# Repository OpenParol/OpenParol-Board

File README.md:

# OpenParol Control board

OpenParol-board is an open-source controller for a 6-DOF robotic arm. It features six TMC5160T Pro drivers and a section containing two galvanically isolated CAN-FD buses, which can be used for communication with external (or future) modules and controllers. It also includes an isolated I/O section for connecting limit switches (both mechanical and NPN inductive types), as well as two galvanically isolated outputs and inputs (one of which supports an MCU interrupt).

> [!IMPORTANT]
> This is merely a hobby project; under no circumstances is it a professional project intended for industrial use!

> [!IMPORTANT]
> The current design is a development version and has not yet been tested. It is therefore best to wait for the official release.

<div align="center">
  <span style="display: inline-block; font-size: 1.25em; font-weight: 600; letter-spacing: 0.7px; margin-bottom: 20px;">Sponsors</span>
  
  <span style="display: inline-block; margin-top: 10px;">Thank you for helping to develop this project!</span>
</div>

---
<br>

<span style="font-size: 1.25em; font-weight: 600; letter-spacing: 0.7px;">🌟 Design compatible with and tested on the PAROL6 arm by [@PCrnjak](https://github.com/PCrnjak). Thank you for such a wonderful project!</span>

## Overview

The board is built around an **STM32G474VET6** microcontroller and is designed
to provide:

- six **TMC5160T** stepper-motor driver channels;
- isolated CAN interfaces using **ISO1042DWV** transceivers;
- galvanic isolation and isolated power rails for selected interfaces;
- USB-C 2.0 connectivity;
- an ARM JTAG/SWD debug connector;
- status indicators, test points, configuration jumpers, and pluggable
  motor/power connectors.

The exact electrical behavior, pin assignments, component values, and
connection details are defined by the KiCad source files and should be taken
from the schematic rather than inferred from this overview.

<span style="font-size: 1.25em; font-weight: 600; letter-spacing: 0.7px;">If you are interested in the software, check out the other repositories [here](https://github.com/orgs/OpenParol/repositories)</span>

## Requirements

- [Latest KiCad](https://www.kicad.org/) version or a compatible version that can open
  the project files;
- the repository cloned with its directory structure preserved, so that the
  project can resolve its custom libraries and 3D models.

## Development workflow

When modifying the design:

1. Make schematic changes first.
2. Annotate and update the PCB from the schematic.
3. Verify footprints, pin assignments, clearances, and isolation boundaries.
4. Review the 3D model placement and board constraints.
5. Run ERC and DRC.
6. Export manufacturing files only from a tagged or otherwise clearly
   identified revision.

Custom symbols and footprints are stored in `board/libraries/`. Their library
paths are configured by `board/sym-lib-table` and `board/fp-lib-table`; avoid
moving these files without updating the corresponding KiCad configuration.

## Contributing

Contributions are more than welcome. Before submitting a change:

- keep schematic and PCB changes synchronized;
- include or update custom library data when a new footprint or symbol is
  required;
- preserve the existing project-relative library paths;
- run ERC and DRC and describe any intentional exceptions;
- explain the changes that have been made.

## License

Unless stated otherwise for a particular third-party asset, this project is
provided under the **GNU General Public License v3.0**. See [LICENSE](LICENSE)
for the complete license text.

Third-party component datasheets, manufacturer models, and other external
assets may be subject to their own terms. Verify their licensing and
redistribution conditions before using them outside this repository.

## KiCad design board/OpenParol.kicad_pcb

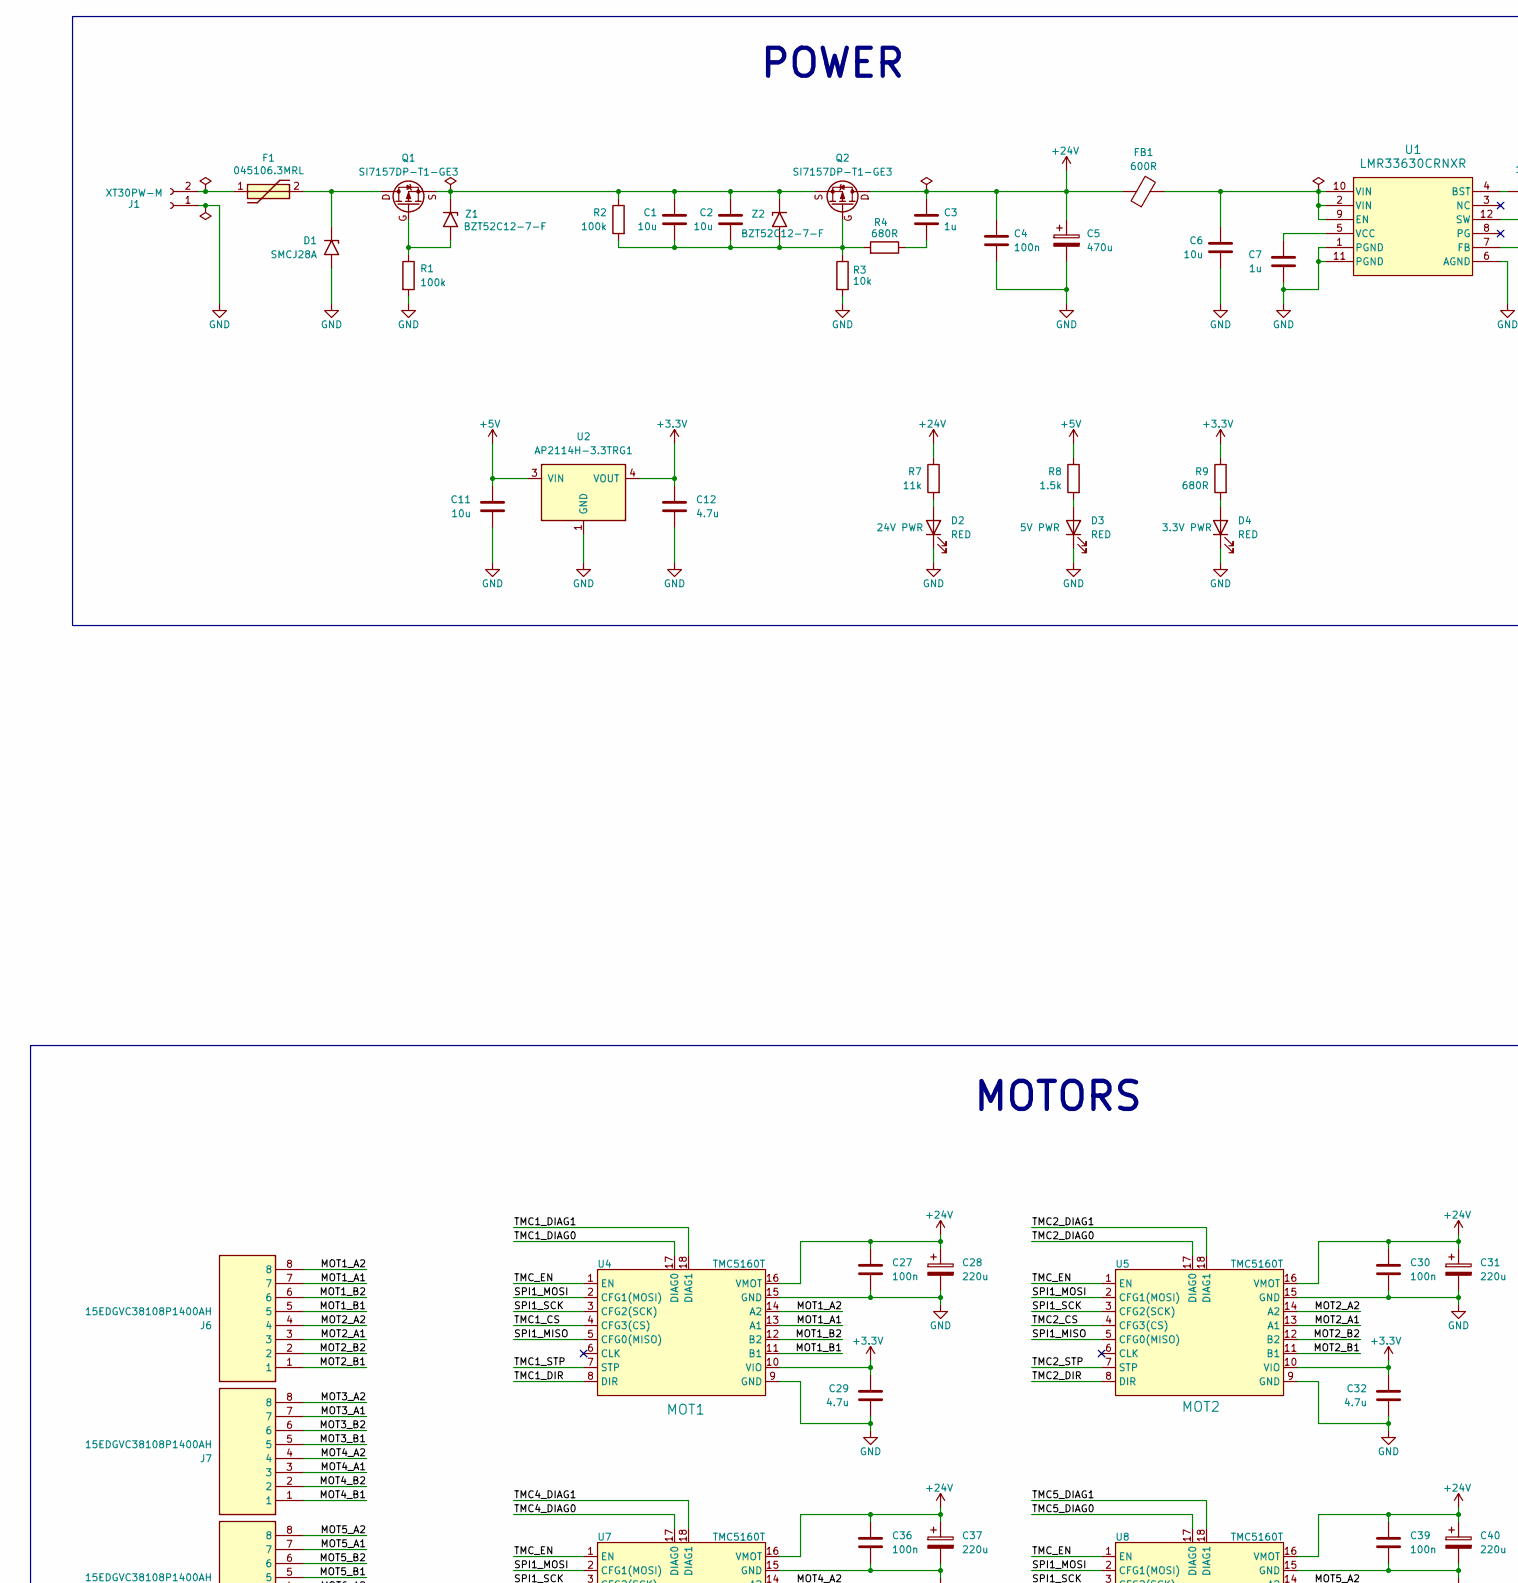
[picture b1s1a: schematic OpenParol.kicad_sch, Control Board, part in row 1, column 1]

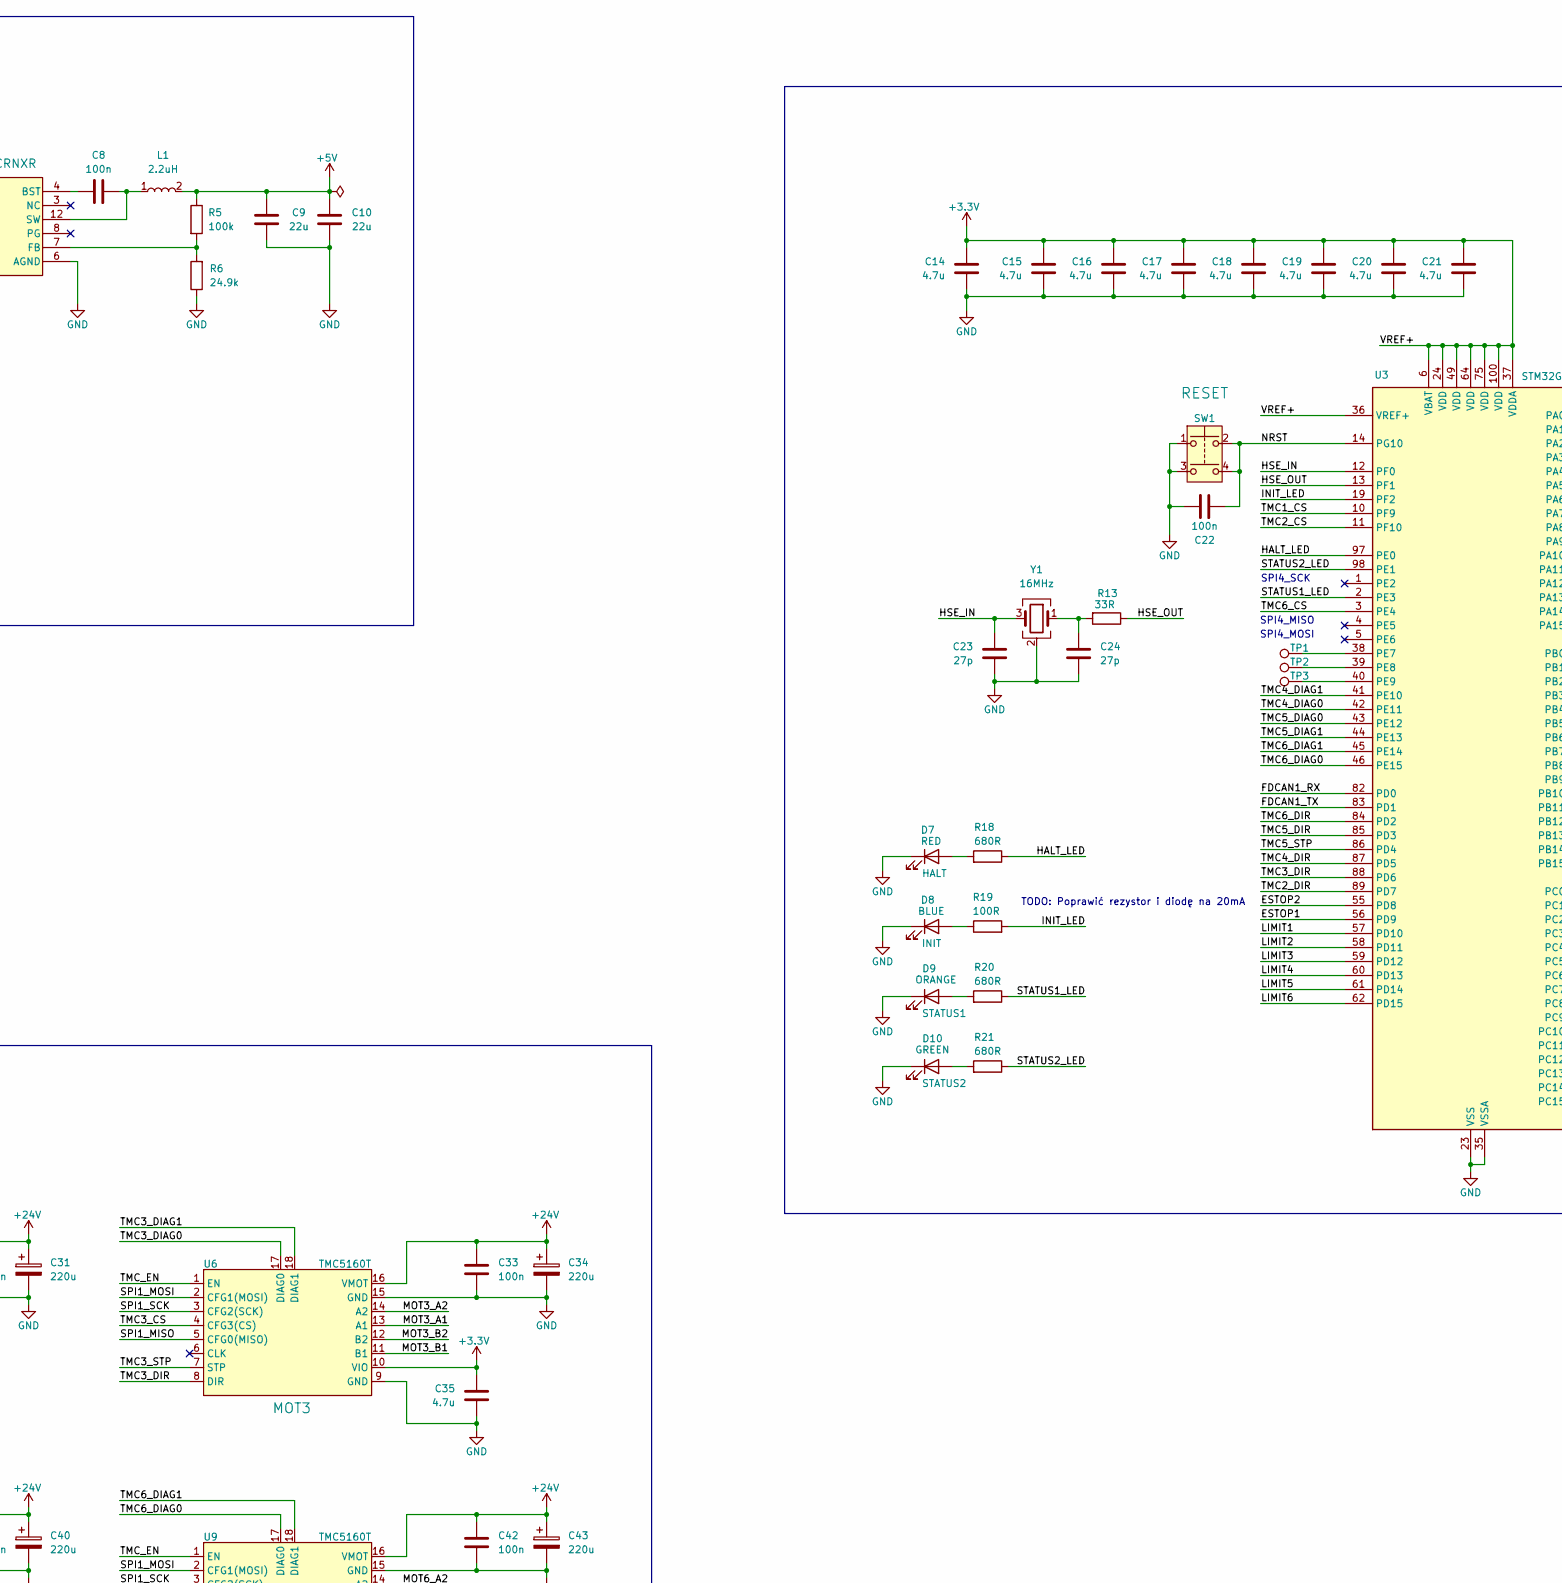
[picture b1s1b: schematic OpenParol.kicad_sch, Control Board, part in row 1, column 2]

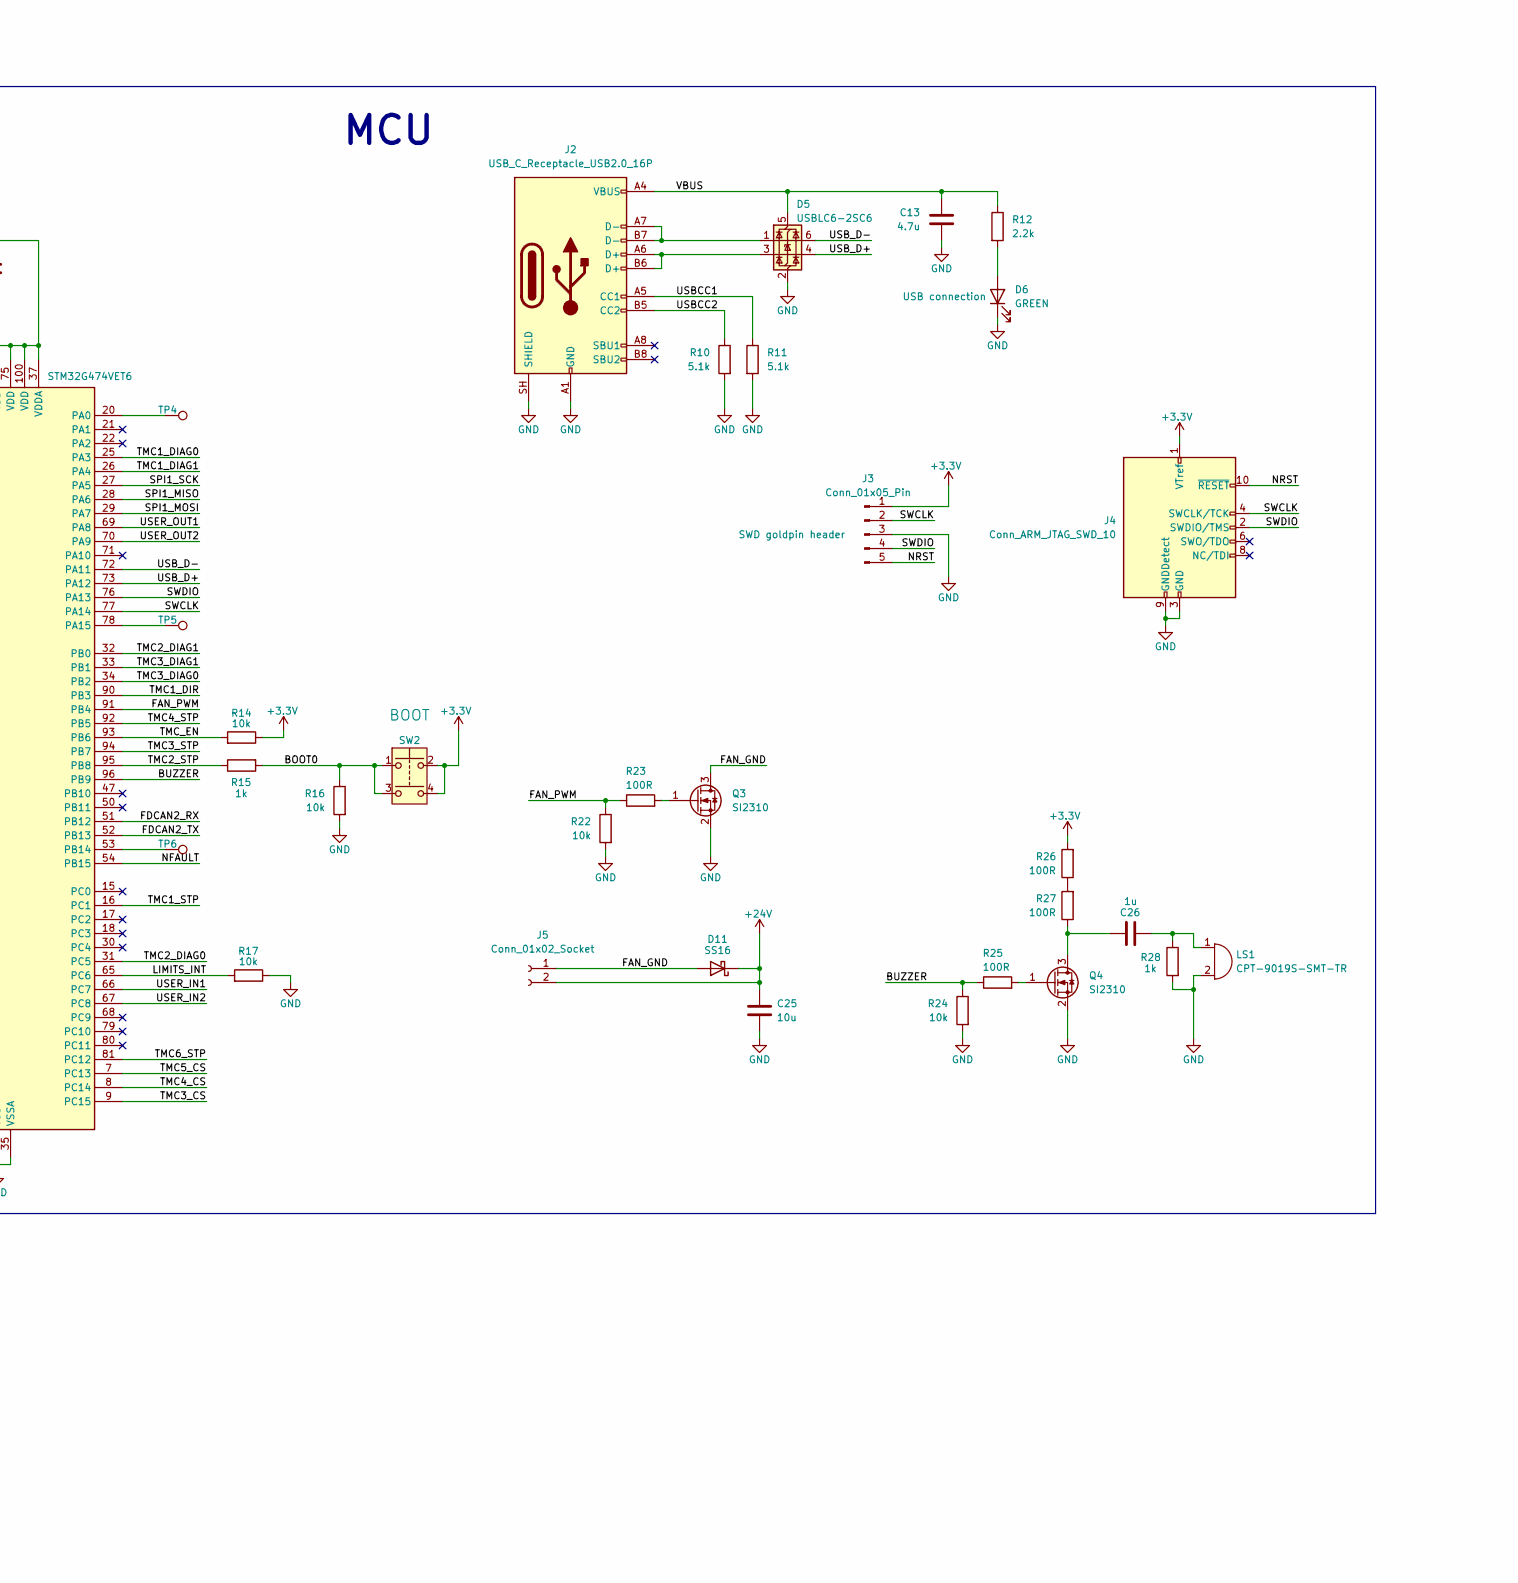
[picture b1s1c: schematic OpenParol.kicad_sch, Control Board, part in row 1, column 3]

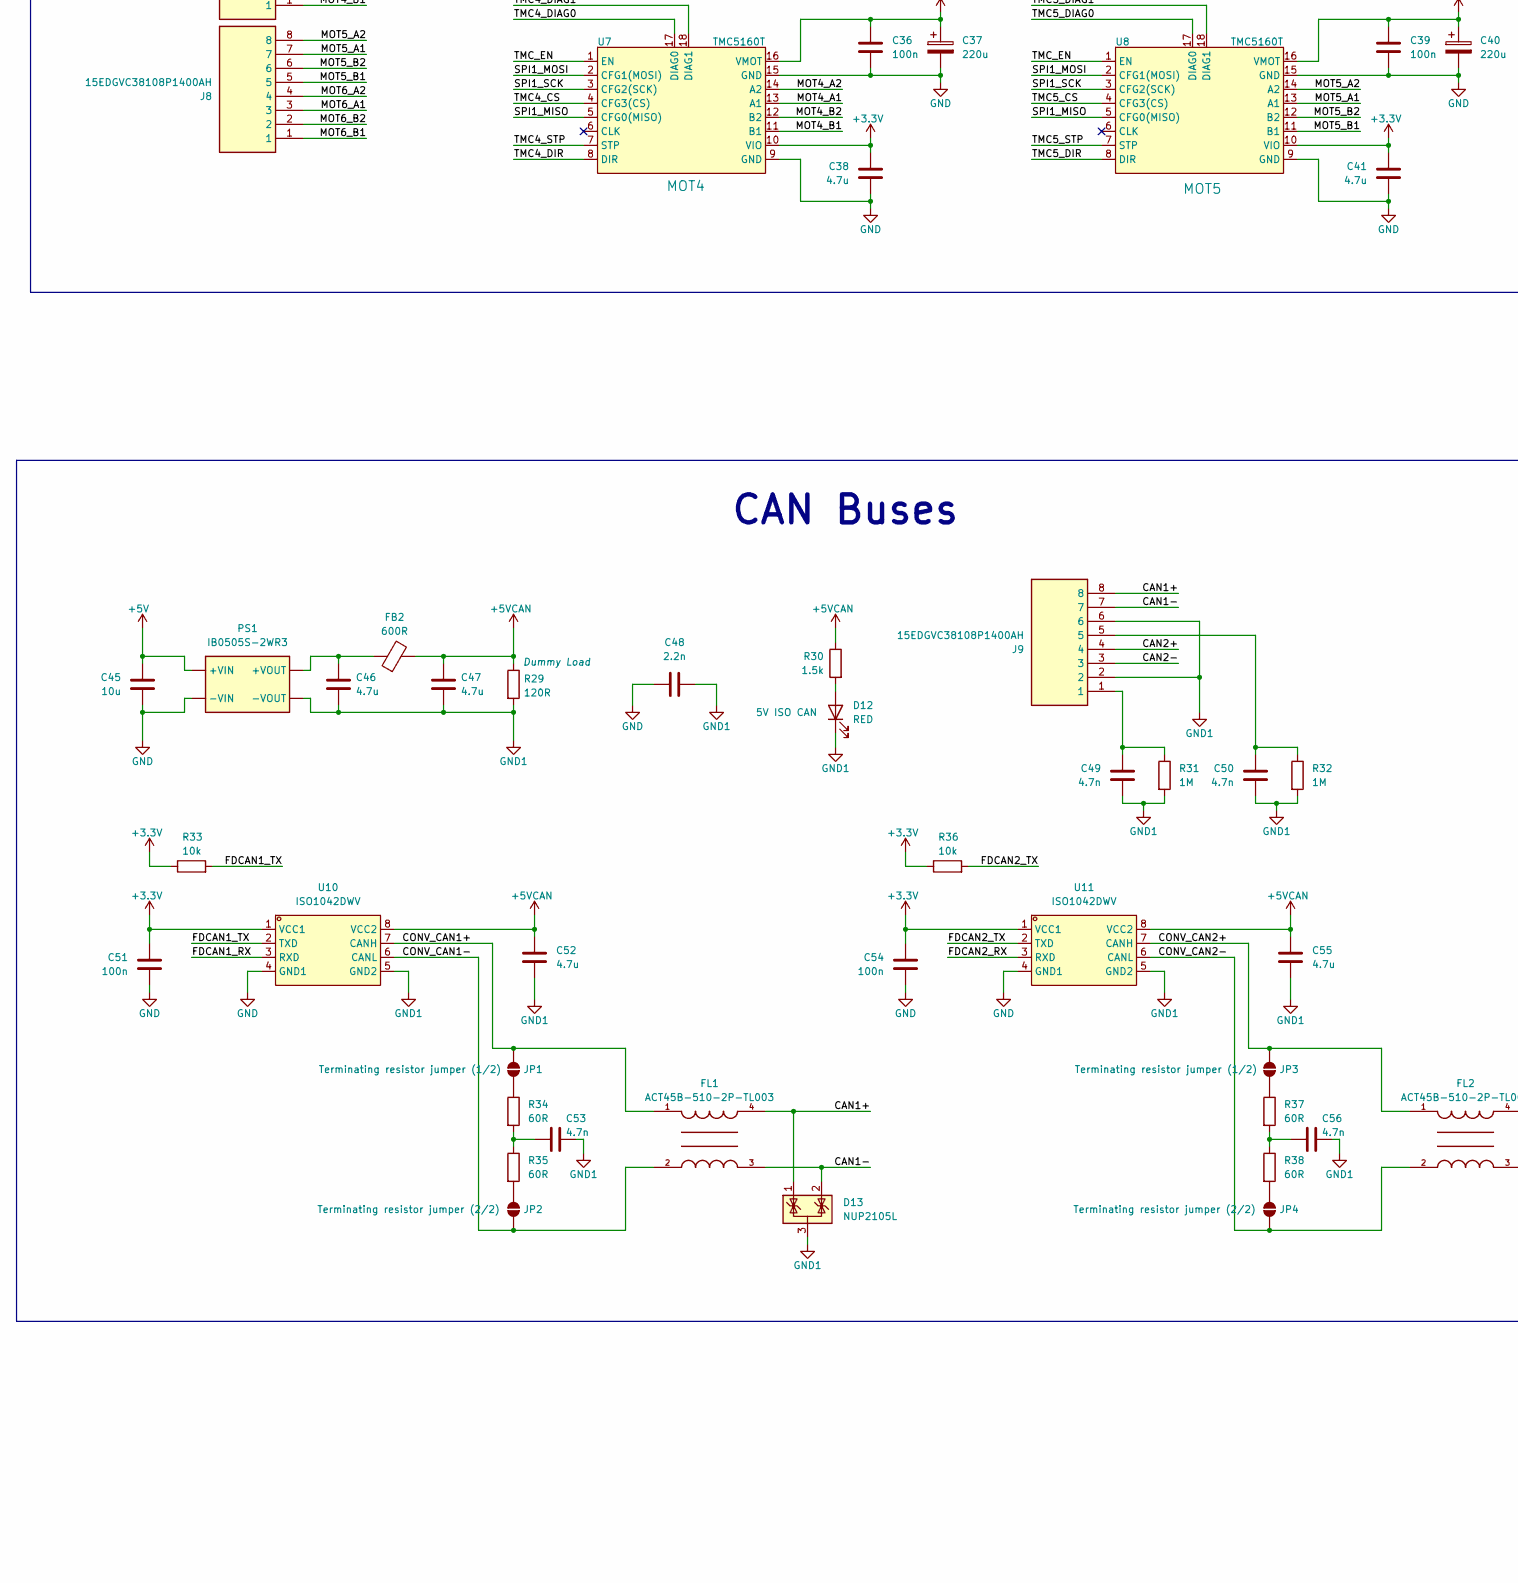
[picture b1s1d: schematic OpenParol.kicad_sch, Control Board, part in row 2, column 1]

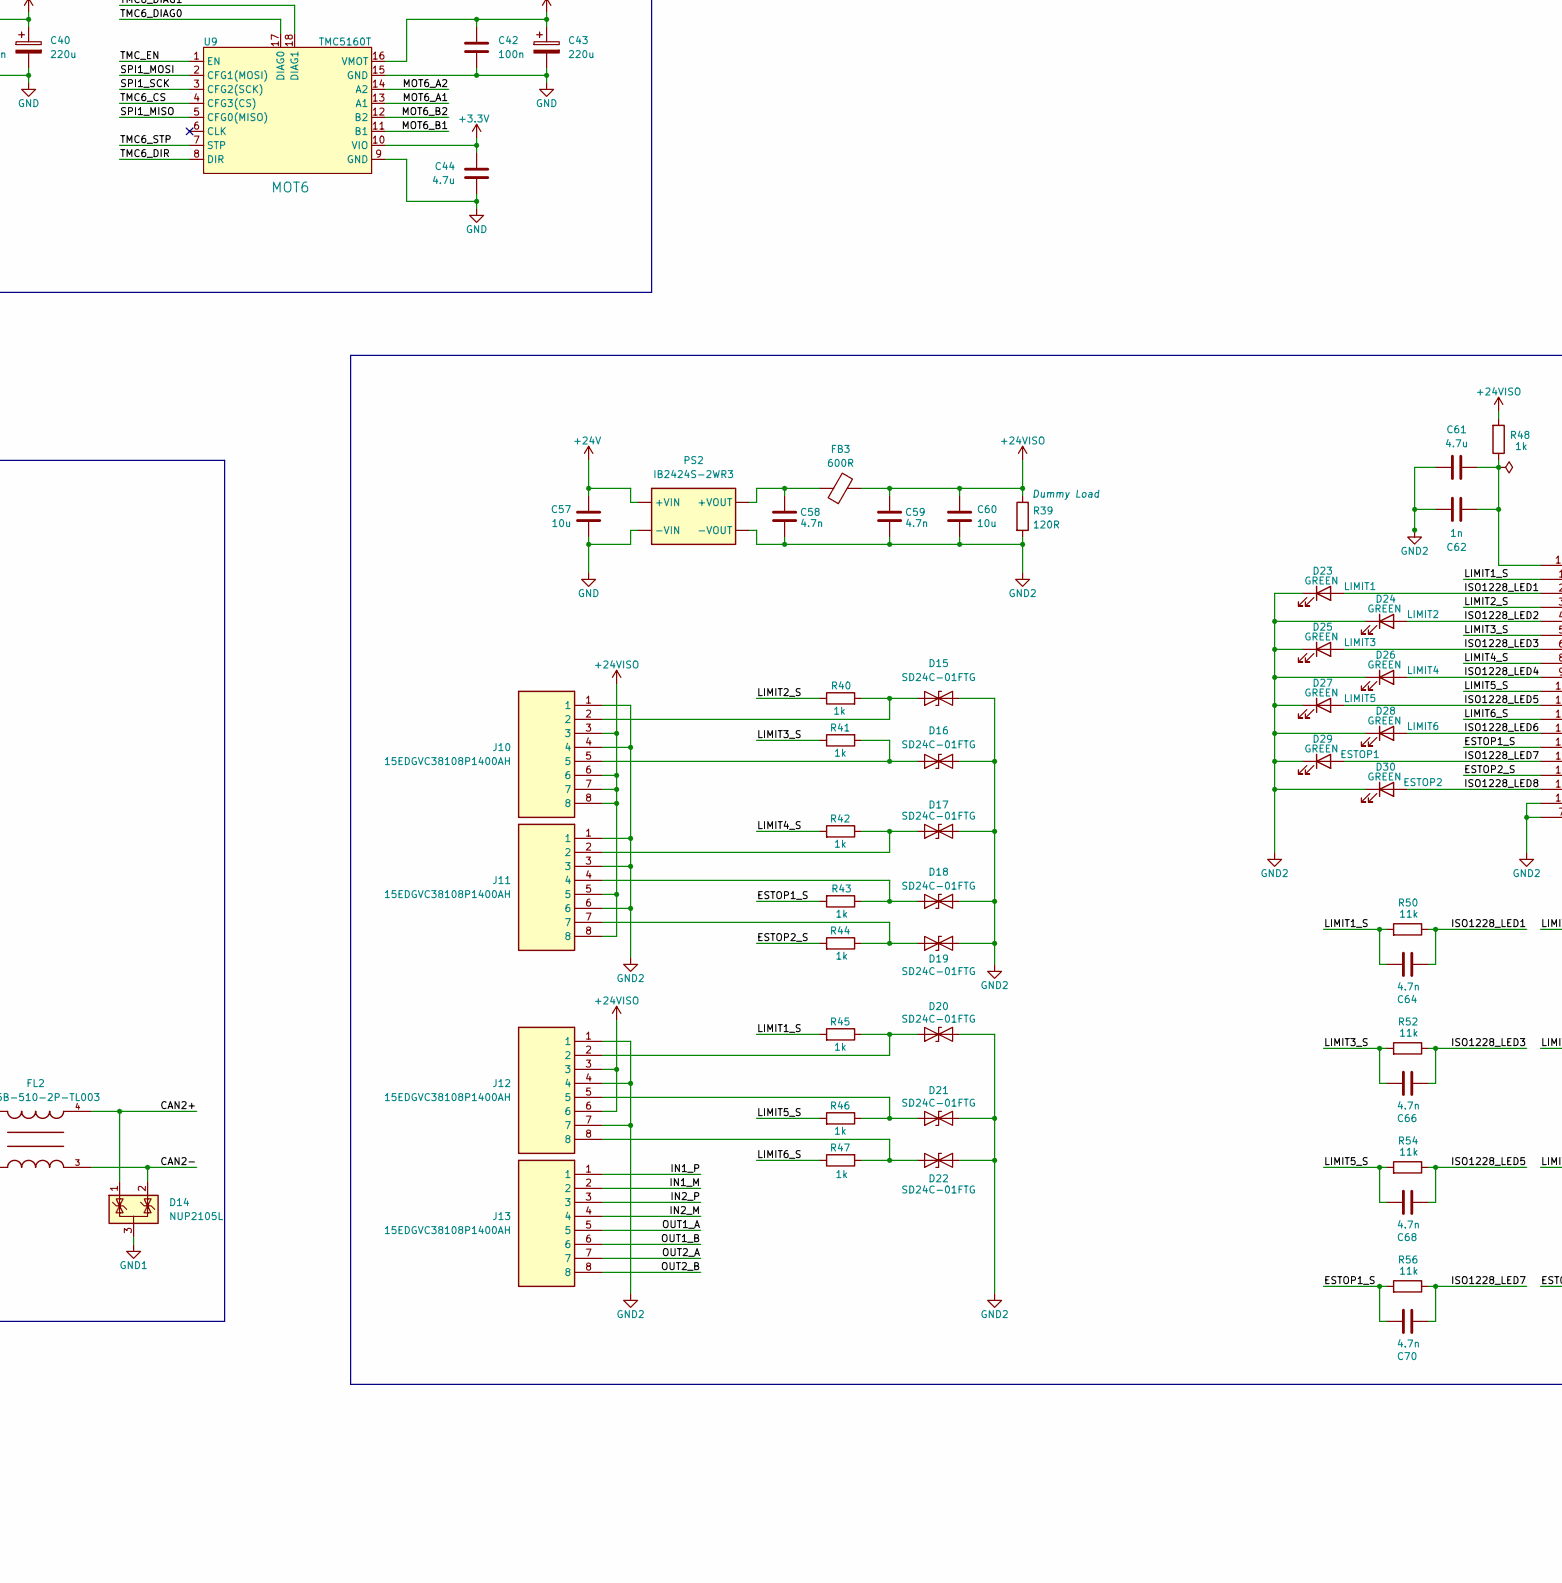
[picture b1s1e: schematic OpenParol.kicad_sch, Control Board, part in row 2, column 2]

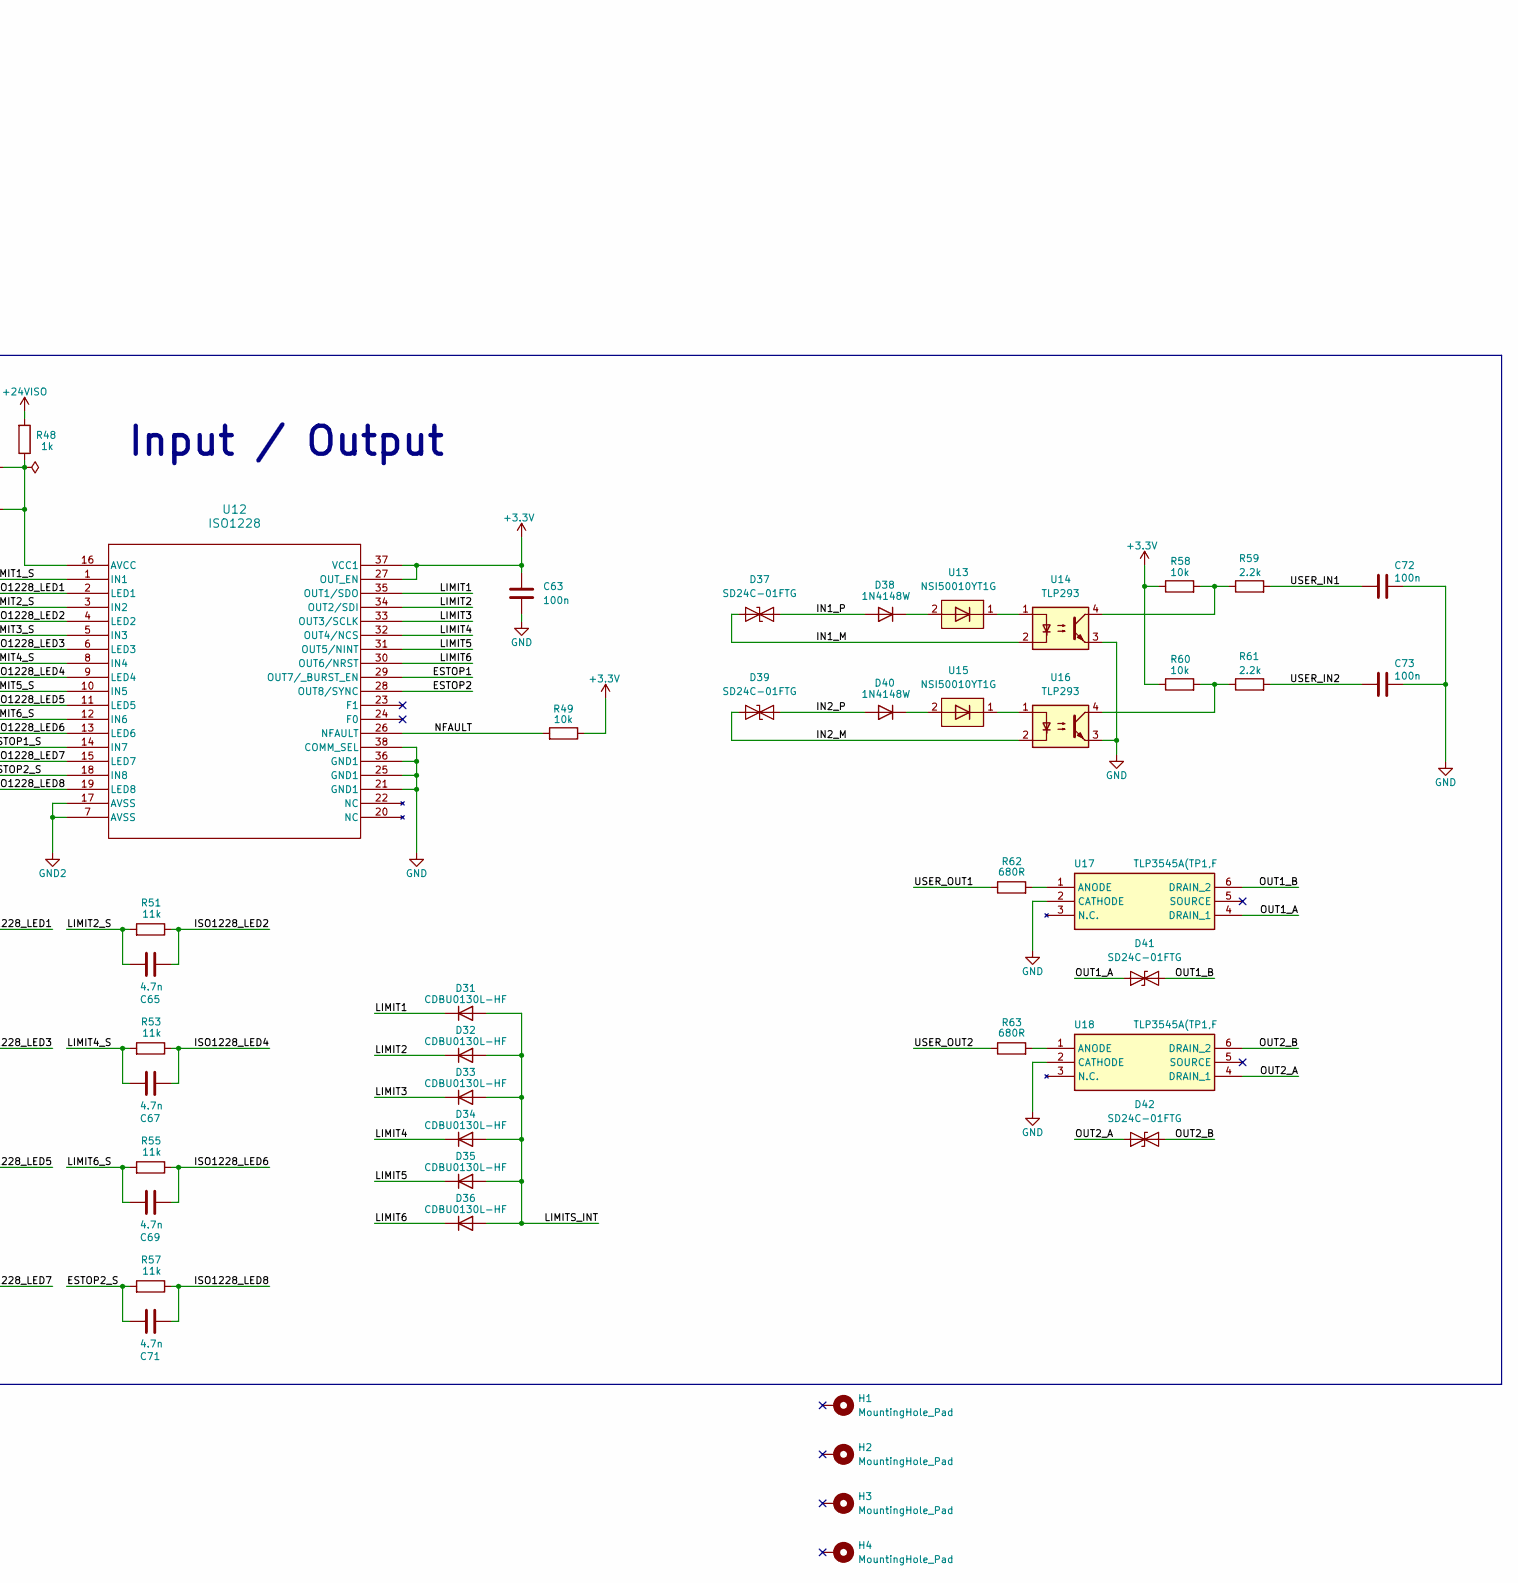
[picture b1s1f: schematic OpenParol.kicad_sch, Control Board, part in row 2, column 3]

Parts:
C1, C2, C6, C25, C57, C60: 10u; C_1210_3225Metric_Pad1.33x2.70mm_HandSolder; MPN CL32B106KBJNNNE
C3: 1u; C_0805_2012Metric_Pad1.18x1.45mm_HandSolder; MPN C0805C105K5RACTU
C4, C27, C30, C33, C36, C39, C42: 100n; C_0805_2012Metric_Pad1.18x1.45mm_HandSolder; MPN C2012X7R2A104M125AA
C5: 470u; CP_Radial_D12.5mm_P5.00mm; MPN EKY-500ELL471MK20S
C7, C26: 1u; C_0805_2012Metric_Pad1.18x1.45mm_HandSolder; MPN GCM21BR71C105KA58K
C8, C22, C51, C54, C63, C72, C73: 100n; C_0603_1608Metric_Pad1.08x0.95mm_HandSolder; MPN 06033C104JAZ2A
C9, C10: 22u; C_1206_3216Metric_Pad1.33x1.80mm_HandSolder; MPN HGC1206R7226K160NSPJ
C11, C45: 10u; C_0805_2012Metric_Pad1.18x1.45mm_HandSolder; MPN CL21B106KOQNNNG
C12, C13, C14, C15, C16, C17, C18, C19, C20, C21, C29, C32, C35, C38, C41, C44, C46, C47, C52, C55: 4.7u; C_0603_1608Metric_Pad1.08x0.95mm_HandSolder; MPN GRM188Z71C475KE21D
C23, C24: 27p; C_0603_1608Metric_Pad1.08x0.95mm_HandSolder; MPN VJ0603D270FXBAJ
C28, C31, C34, C37, C40, C43: 220u; CP_Elec_10x10.5; MPN HV1H227M1010PZ
C48: 2.2n; C_1812_4532Metric_Pad1.57x3.40mm_HandSolder; MPN 885342211010
C49, C50: 4.7n; C_1206_3216Metric_Pad1.33x1.80mm_HandSolder; MPN 12067C472KAT2A
C53, C56, C58, C59, C64, C65, C66, C67, C68, C69, C70, C71: 4.7n; C_0603_1608Metric_Pad1.08x0.95mm_HandSolder; MPN 06035C472JAT2A
C61: 4.7u; C_0805_2012Metric_Pad1.18x1.45mm_HandSolder; MPN 0805B475K500NT
C62: 1n; C_0805_2012Metric_Pad1.18x1.45mm_HandSolder; MPN CL21B102KBANNNC
D1: SMCJ28A
D2, D3, D4, D7, D12: RED; LED_0603_1608Metric_Pad1.05x0.95mm_HandSolder; MPN SML-D14VWT86C
D5: USBLC6-2SC6; SOT-23-6
D6, D10, D23, D24, D25, D26, D27, D28, D29, D30: GREEN; LED_0603_1608Metric_Pad1.05x0.95mm_HandSolder; MPN SML-D12FWT86
D8: BLUE; LED_0603_1608Metric_Pad1.05x0.95mm_HandSolder; MPN SMLEN3BC8TT86
D9: ORANGE; LED_0603_1608Metric_Pad1.05x0.95mm_HandSolder; MPN D-060306U1/SS2/U
D11: SS16; D_SMA; MPN SS16
D13, D14: NUP2105L; SOT-23; MPN NUP2105LT1G
D15, D16, D17, D18, D19, D20, D21, D22, D37, D39, D41, D42: SD24C-01FTG; D_SOD-323; MPN SD24C-01FTG
D31, D32, D33, D34, D35, D36: CDBU0130L-HF; D_0603_1608Metric_Pad1.05x0.95mm_HandSolder; MPN CDBU0130L-HF
D38, D40: 1N4148W; D_SOD-123; MPN 1N4148W
F1: 045106.3MRL; Mouser Part Number 576-045106.3MRL
FB1, FB2, FB3: 600R; L_0805_2012Metric_Pad1.05x1.20mm_HandSolder; MPN 74279220601
FL1, FL2: ACT45B-510-2P-TL003; PARTREV 20200405
H1, H2, H3, H4: MountingHole_Pad; MountingHole_3.2mm_M3_Pad_Via
J1: XT30PW-M; AMASS_XT30PW-M_1x02_P2.50mm_Horizontal; MPN XT30PW-M
J2: USB_C_Receptacle_USB2.0_16P; USB_C_Receptacle_GCT_USB4105-xx-A_16P_TopMnt_Horizontal
J3: Conn_01x05_Pin; PinHeader_1x05_P2.54mm_Vertical
J4: Conn_ARM_JTAG_SWD_10; IDC-Header_2x05_P2.54mm_Horizontal
J5: Conn_01x02_Socket; JST_XH_B2B-XH-A_1x02_P2.50mm_Vertical
J6, J7, J8, J9, J10, J11, J12, J13: 15EDGVC38108P1400AH; Manufacturer_Part_Number 15EDGVC-3.81-08P-14-00A(H)
JP1, JP2, JP3, JP4: SolderJumper_2_Open; SolderJumper-2_P1.3mm_Open_TrianglePad1.0x1.5mm
L1: 2.2uH; SRP5030CA-2R2M; Manufacturer_Part_Number SRP5030CA-2R2M; Mouser Part Number 652-SRP5030CA-2R2M
LS1: CPT-9019S-SMT-TR; PART_REV 1.0
PS1: IB0505S-2WR3; Manufacturer_Part_Number IB0505S-2WR3
PS2: IB2424S-2WR3; Manufacturer_Part_Number IB2424S-2WR3
Q1, Q2: SI7157DP-T1-GE3; Mouser Part Number 78-SI7157DP-T1-GE3
Q3, Q4: SI2310; SOT-23-3; MPN SI2310
R1, R2, R5: 100k; R_0603_1608Metric_Pad0.98x0.95mm_HandSolder; MPN RN73H1JTTD1003B25
R3, R14, R16, R17, R22, R24, R33, R36, R49, R58, R60: 10k; R_0603_1608Metric_Pad0.98x0.95mm_HandSolder; MPN CRCW060310K0FKEAHP
R4, R9, R18, R20, R21, R62, R63: 680R; R_0603_1608Metric_Pad0.98x0.95mm_HandSolder; MPN WR06X6800FTL
R6: 24.9k; R_0603_1608Metric_Pad0.98x0.95mm_HandSolder; MPN ERA-3AEB2492V
R7, R50, R51, R52, R53, R54, R55, R56, R57: 11k; R_0603_1608Metric_Pad0.98x0.95mm_HandSolder; MPN ERA-3AEB113V
R8, R30: 1.5k; R_0603_1608Metric_Pad0.98x0.95mm_HandSolder; MPN RMCF0603FT1K50
R10, R11: 5.1k; R_0603_1608Metric_Pad0.98x0.95mm_HandSolder; MPN RK73H1JTTD5101F
R12, R59, R61: 2.2k; R_0603_1608Metric_Pad0.98x0.95mm_HandSolder; MPN CR0603-FX-2201ELF
R13: 33R; R_0603_1608Metric_Pad0.98x0.95mm_HandSolder; MPN CPF0603B33RE
R15, R28, R40, R41, R42, R43, R44, R45, R46, R47, R48: 1k; R_0603_1608Metric_Pad0.98x0.95mm_HandSolder; MPN CRGH0603F1K0
R19, R23, R25, R26, R27: 100R; R_0603_1608Metric_Pad0.98x0.95mm_HandSolder; MPN CR0603-FX-1000ELF
R29, R39: 120R; R_1206_3216Metric_Pad1.30x1.75mm_HandSolder; MPN CRGH1206J120R
R31, R32: 1M; R_1206_3216Metric_Pad1.30x1.75mm_HandSolder; MPN HV732BTTD1004F
R34, R35, R37, R38: 60R; R_0603_1608Metric_Pad0.98x0.95mm_HandSolder; MPN RTT0360R0FTP
SW1, SW2: PTS647SN50SMTR2 LFS; MPN PTS647SN50SMTR2 LFS
TP1: PE7; TestPoint_Pad_D1.5mm
TP2: PE8; TestPoint_Pad_D1.5mm
TP3: PE9; TestPoint_Pad_D1.5mm
TP4: PA0; TestPoint_Pad_D1.5mm
TP5: PA15; TestPoint_Pad_D1.5mm
TP6: PB14; TestPoint_Pad_D1.5mm
U1: LMR33630CRNXR
U2: AP2114H-3.3TRG1; Manufacturer_Part_Number AP2114H-3.3TRG1
U3: STM32G474VET6; LQFP-100_14x14mm_P0.5mm
U4, U5, U6, U7, U8, U9: TMC5160T; TMC5160T_PRO
U10, U11: ISO1042DWV; MPN ISO1042DWV
U12: ISO1228
U13, U15: NSI50010YT1G; D_SOD-123; MPN NSI50010YT1G
U14, U16: TLP293; SOIC-4_4.55x2.6mm_P1.27mm; MPN TLP293(GR-TPL,E
U17, U18: TLP3545A(TP1,F; Mouser Part Number 757-TLP3545ATP1F
Y1: 16MHz; Crystal_SMD_3225-4Pin_3.2x2.5mm; MPN 7M-16.000MAAJ-T
Z1, Z2: BZT52C12-7-F; Mouser Part Number 621-BZT52C12-F

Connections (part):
+3.3V: C12.1, C14.1, C15.1, C16.1, C17.1, C18.1, C19.1, C20.1, C21.1, C29.1, C32.1, C35.1, C38.1, C41.1, C44.1, C51.1, C54.1, C63.1, J3.1, J4.1 (VTref), R9.1, R14.1, R26.2, R33.1, R36.1, R49.1, R58.1, R60.1, SW2.2, SW2.4, U2.2 (VOUT), U2.4 (VOUT), U3.6 (VBAT), U3.24 (VDD), U3.36 (VREF+), U3.37 (VDDA), U3.49 (VDD), U3.64 (VDD), U3.75 (VDD), U3.100 (VDD), U4.10 (VIO), U5.10 (VIO), U6.10 (VIO), U7.10 (VIO), U8.10 (VIO), U9.10 (VIO), U10.1 (VCC1), U11.1 (VCC1), U12.27 (OUT_EN), U12.37 (VCC1)
+5V: C9.2, C10.2, C11.1, C45.1, L1.2, PS1.1 (+VIN), R5.1, R8.1, U2.3 (VIN)
+5VCAN: C47.1, C52.1, C55.1, FB2.2, R29.1, R30.1, U10.8 (VCC2), U11.8 (VCC2)
+24V: C3.1, C4.1, C5.1, C25.1, C27.1, C28.1, C30.1, C31.1, C33.1, C34.1, C36.1, C37.1, C39.1, C40.1, C42.1, C43.1, C57.1, D11.1 (K), FB1.1, J5.2, PS2.1 (+VIN), Q2.5 (D), Q2.6 (D_2), Q2.7 (D_3), Q2.8 (D_4), Q2.9 (Thermal_pad), R7.1, U4.16 (VMOT), U5.16 (VMOT), U6.16 (VMOT), U7.16 (VMOT), U8.16 (VMOT), U9.16 (VMOT)
+24VISO: C59.1, C60.1, FB3.2, J10.3, J10.6, J10.7, J10.8, J11.5, J11.8, J12.3, J12.6, R39.1, R48.2
/BOOT0: R15.2, R16.1, SW2.1, SW2.3
/BUZZER: R24.1, R25.1, U3.96 (PB9)
/CAN1+: D13.1 (K), FL1.4, J9.8
/CAN1-: D13.2 (K), FL1.3, J9.7
/CAN2+: D14.1 (K), FL2.4, J9.4
/CAN2-: D14.2 (K), FL2.3, J9.3
/CONV_CAN1+: FL1.1, JP1.2 (B), U10.7 (CANH)
/CONV_CAN1-: FL1.2, JP2.1 (A), U10.6 (CANL)
/CONV_CAN2+: FL2.1, JP3.2 (B), U11.7 (CANH)
/CONV_CAN2-: FL2.2, JP4.1 (A), U11.6 (CANL)
/ESTOP1: U3.56 (PD9), U12.29 (OUT7/_BURST_EN)
/ESTOP1_S: C70.2, R43.2, R56.2, U12.14 (IN7)
/ESTOP2: U3.55 (PD8), U12.28 (OUT8/SYNC)
/ESTOP2_S: C71.2, R44.2, R57.2, U12.18 (IN8)
/FAN_GND: D11.2 (A), J5.1, Q3.3 (D)
/FAN_PWM: R22.1, R23.1, U3.91 (PB4)
/FDCAN1_RX: U3.82 (PD0), U10.3 (RXD)
/FDCAN1_TX: R33.2, U3.83 (PD1), U10.2 (TXD)
/FDCAN2_RX: U3.51 (PB12), U11.3 (RXD)
/FDCAN2_TX: R36.2, U3.52 (PB13), U11.2 (TXD)
/HALT_LED: R18.1, U3.97 (PE0)
/HSE_IN: C23.1, U3.12 (PF0), Y1.3
/HSE_OUT: R13.1, U3.13 (PF1)
/IN1_M: D37.2 (A2), J13.2, U14.2
/IN1_P: D37.1 (A1), D38.2 (A), J13.1
/IN2_M: D39.2 (A2), J13.4, U16.2
/IN2_P: D39.1 (A1), D40.2 (A), J13.3
/INIT_LED: R19.2, U3.19 (PF2)
/ISO1228_LED1: C64.1, D23.2 (A), R50.1, U12.2 (LED1)
/ISO1228_LED2: C65.1, D24.2 (A), R51.1, U12.4 (LED2)
/ISO1228_LED3: C66.1, D25.2 (A), R52.1, U12.6 (LED3)
/ISO1228_LED4: C67.1, D26.2 (A), R53.1, U12.9 (LED4)
/ISO1228_LED5: C68.1, D27.2 (A), R54.1, U12.11 (LED5)
/ISO1228_LED6: C69.1, D28.2 (A), R55.1, U12.13 (LED6)
/ISO1228_LED7: C70.1, D29.2 (A), R56.1, U12.15 (LED7)
/ISO1228_LED8: C71.1, D30.2 (A), R57.1, U12.19 (LED8)
/LIMIT1: D31.1 (K), U3.57 (PD10), U12.35 (OUT1/SDO)
/LIMIT1_S: C64.2, R45.2, R50.2, U12.1 (IN1)
/LIMIT2: D32.1 (K), U3.58 (PD11), U12.34 (OUT2/SDI)
/LIMIT2_S: C65.2, R40.1, R51.2, U12.3 (IN2)
/LIMIT3: D33.1 (K), U3.59 (PD12), U12.33 (OUT3/SCLK)
/LIMIT3_S: C66.2, R41.1, R52.2, U12.5 (IN3)
/LIMIT4: D34.1 (K), U3.60 (PD13), U12.32 (OUT4/NCS)
/LIMIT4_S: C67.2, R42.2, R53.2, U12.8 (IN4)
/LIMIT5: D35.1 (K), U3.61 (PD14), U12.31 (OUT5/NINT)
/LIMIT5_S: C68.2, R46.2, R54.2, U12.10 (IN5)
/LIMIT6: D36.1 (K), U3.62 (PD15), U12.30 (OUT6/NRST)
/LIMIT6_S: C69.2, R47.1, R55.2, U12.12 (IN6)
/LIMITS_INT: D31.2 (A), D32.2 (A), D33.2 (A), D34.2 (A), D35.2 (A), D36.2 (A), R17.2, U3.65 (PC6)
/MOT1_A1: J6.7, U4.13 (A1)
/MOT1_A2: J6.8, U4.14 (A2)
/MOT1_B1: J6.5, U4.11 (B1)
/MOT1_B2: J6.6, U4.12 (B2)
/MOT2_A1: J6.3, U5.13 (A1)
/MOT2_A2: J6.4, U5.14 (A2)
/MOT2_B1: J6.1, U5.11 (B1)
/MOT2_B2: J6.2, U5.12 (B2)
/MOT3_A1: J7.7, U6.13 (A1)
/MOT3_A2: J7.8, U6.14 (A2)
/MOT3_B1: J7.5, U6.11 (B1)
/MOT3_B2: J7.6, U6.12 (B2)
/MOT4_A1: J7.3, U7.13 (A1)
/MOT4_A2: J7.4, U7.14 (A2)
/MOT4_B1: J7.1, U7.11 (B1)
/MOT4_B2: J7.2, U7.12 (B2)
/MOT5_A1: J8.7, U8.13 (A1)
/MOT5_A2: J8.8, U8.14 (A2)
/MOT5_B1: J8.5, U8.11 (B1)
/MOT5_B2: J8.6, U8.12 (B2)
/MOT6_A1: J8.3, U9.13 (A1)
/MOT6_A2: J8.4, U9.14 (A2)
/MOT6_B1: J8.1, U9.11 (B1)
/MOT6_B2: J8.2, U9.12 (B2)
/NFAULT: R49.2, U3.54 (PB15), U12.26 (NFAULT)
/NRST: C22.2, J3.5, J4.10 (~RESET), SW1.2, SW1.4, U3.14 (PG10)
/OUT1_A: D41.1 (A1), J13.5, U17.4 (DRAIN_1)
/OUT1_B: D41.2 (A2), J13.6, U17.6 (DRAIN_2)
/OUT2_A: D42.1 (A1), J13.7, U18.4 (DRAIN_1)
/OUT2_B: D42.2 (A2), J13.8, U18.6 (DRAIN_2)
/SPI1_MISO: U3.28 (PA6), U4.5 (CFG0(MISO)), U5.5 (CFG0(MISO)), U6.5 (CFG0(MISO)), U7.5 (CFG0(MISO)), U8.5 (CFG0(MISO)), U9.5 (CFG0(MISO))
/SPI1_MOSI: U3.29 (PA7), U4.2 (CFG1(MOSI)), U5.2 (CFG1(MOSI)), U6.2 (CFG1(MOSI)), U7.2 (CFG1(MOSI)), U8.2 (CFG1(MOSI)), U9.2 (CFG1(MOSI))
/SPI1_SCK: U3.27 (PA5), U4.3 (CFG2(SCK)), U5.3 (CFG2(SCK)), U6.3 (CFG2(SCK)), U7.3 (CFG2(SCK)), U8.3 (CFG2(SCK)), U9.3 (CFG2(SCK))
/STATUS1_LED: R20.1, U3.2 (PE3)
/STATUS2_LED: R21.1, U3.98 (PE1)
/SWCLK: J3.2, J4.4 (SWCLK/TCK), U3.77 (PA14)
/SWDIO: J3.4, J4.2 (SWDIO/TMS), U3.76 (PA13)
/TMC1_CS: U3.10 (PF9), U4.4 (CFG3(CS))
/TMC1_DIAG0: U3.25 (PA3), U4.17 (DIAG0)
/TMC1_DIAG1: U3.26 (PA4), U4.18 (DIAG1)
/TMC1_DIR: U3.90 (PB3), U4.8 (DIR)
/TMC1_STP: U3.16 (PC1), U4.7 (STP)
/TMC2_CS: U3.11 (PF10), U5.4 (CFG3(CS))
/TMC2_DIAG0: U3.31 (PC5), U5.17 (DIAG0)
/TMC2_DIAG1: U3.32 (PB0), U5.18 (DIAG1)
/TMC2_DIR: U3.89 (PD7), U5.8 (DIR)
/TMC2_STP: R15.1, U3.95 (PB8), U5.7 (STP)
/TMC3_CS: U3.9 (PC15), U6.4 (CFG3(CS))
/TMC3_DIAG0: U3.34 (PB2), U6.17 (DIAG0)
/TMC3_DIAG1: U3.33 (PB1), U6.18 (DIAG1)
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
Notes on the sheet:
CAN Buses
MCU
TODO: Poprawić rezystor i diodę na 20mA
POWER
Input / Output
SPI4_MOSI
SPI4_SCK
SPI4_MISO
MOTORS

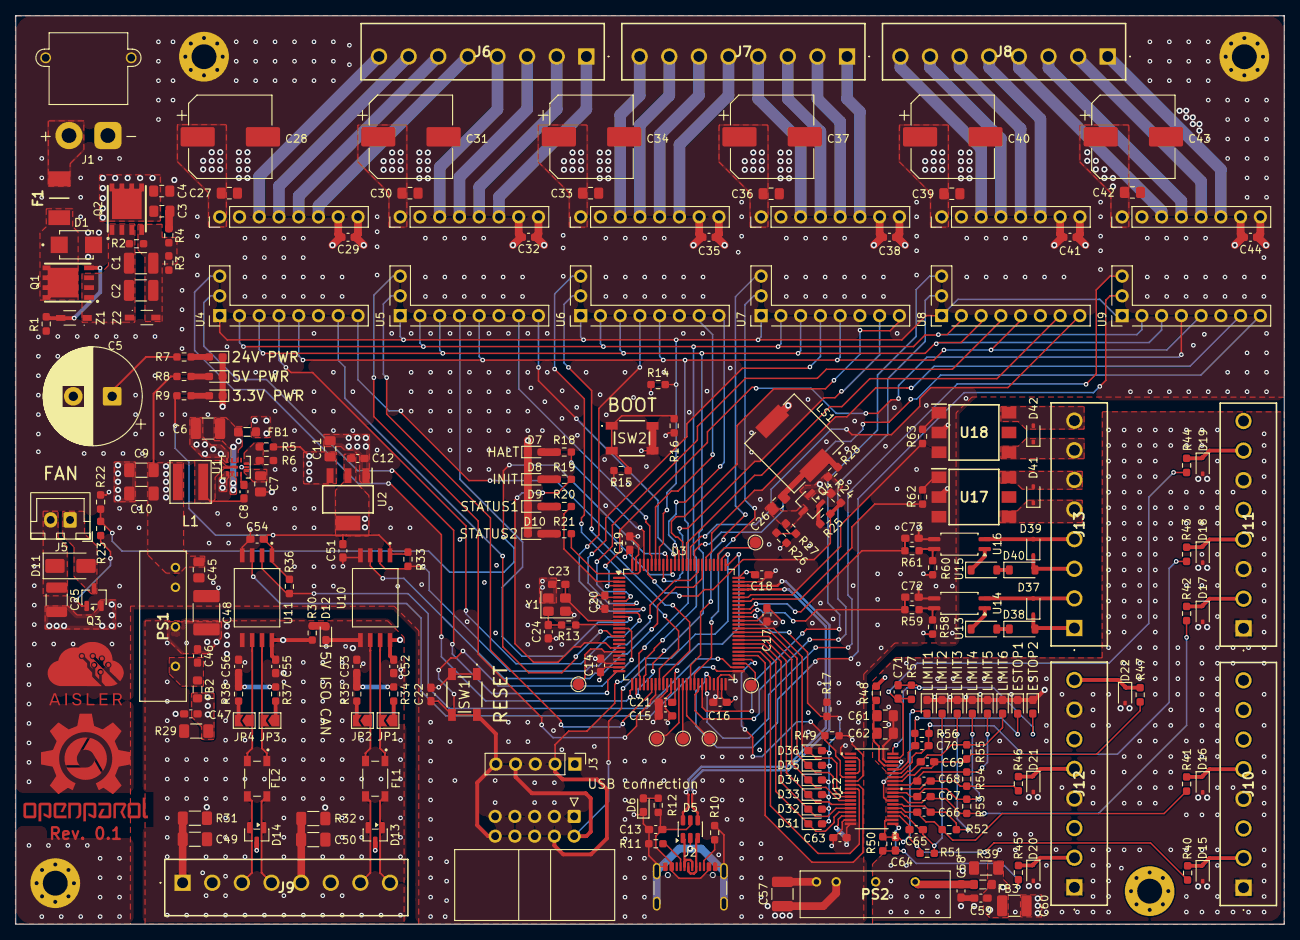
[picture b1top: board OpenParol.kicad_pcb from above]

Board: 4 copper layers, 163.1 x 116.8 mm, 242 parts (0 on the bottom side), 195 nets.
